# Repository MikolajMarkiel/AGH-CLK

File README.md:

# AGH-CLK
Tiny project of embedded wristwatch based on STM32 realised for University - course Design-Laboratory

## Project assumptions
The main goal was to make self-contained embedded wristwatch module that could be used with dedicated wrist as a complete wristwatch

## Technical specification
-	LCD screen 240x240 1,3 inches
-	Clock precision: -6 sec/day (would be better with capacitor corrections)
-	Current consumption: 54,5 mA (without sleep feature)
-	Estimated lifetime per cycle – around 9h (would be better with implemented sleep feature)
-	Charging: 5 VDC; 400 mA; around 75 minutes to full charge battery 500mAh 

## Overview
This project has been designed for purpose of learning STM32 programming and designing PCB with KiCad software. It won't be supported or improved in future. 
There are many mistakes such as huge current consumption, clock precision or aliased display. It could be of course improved for example by adding sleep feature, but it is not necessary to do right now, because others projects also wait to be designed. 

For more information about the project lets read AGH-CLK-Design_Process_Specification inside "Documentation" folder.

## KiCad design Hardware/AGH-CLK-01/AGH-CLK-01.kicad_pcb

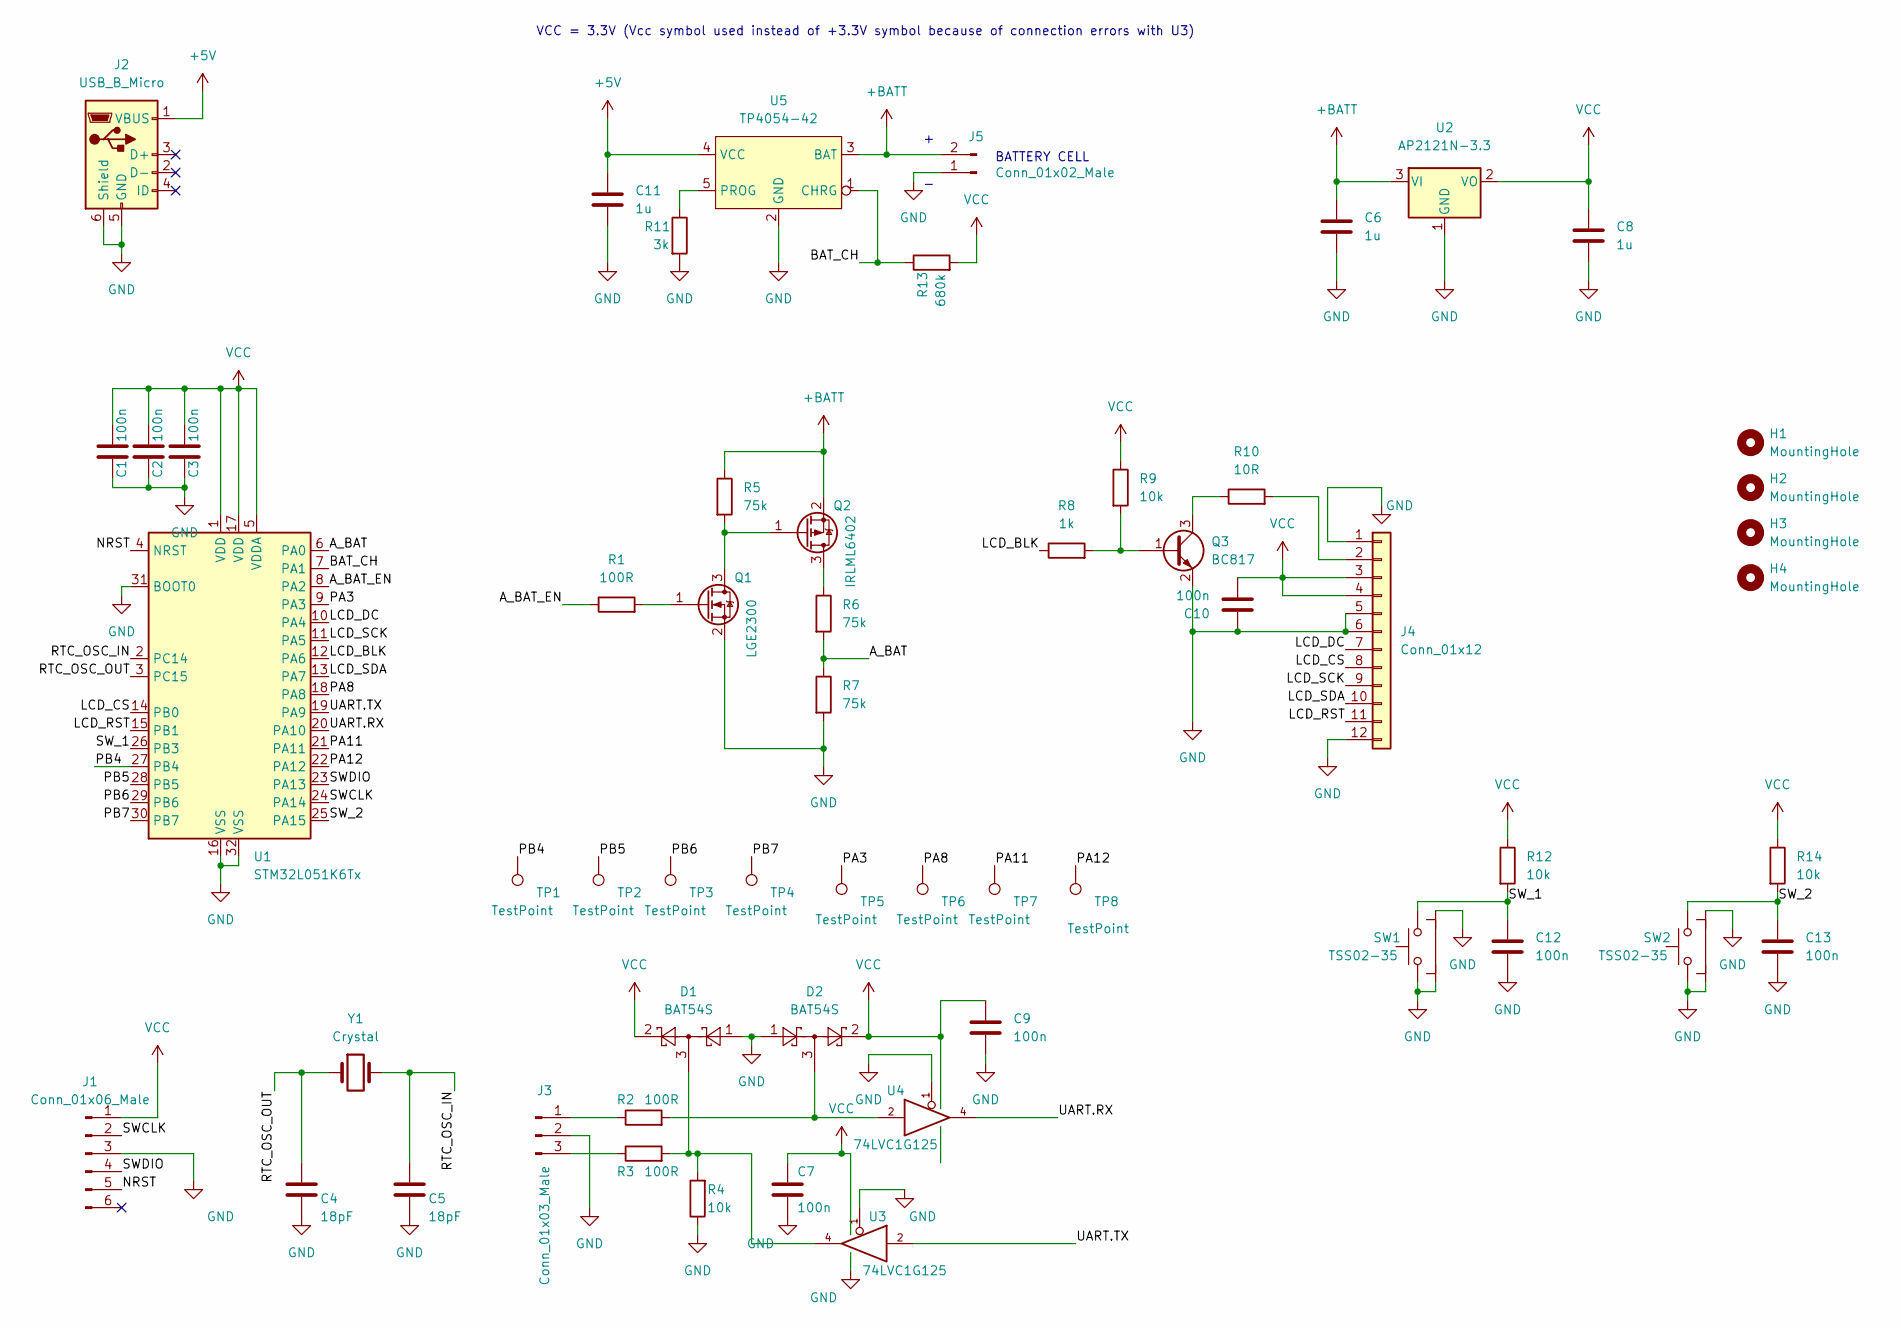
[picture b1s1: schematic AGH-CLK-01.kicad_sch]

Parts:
C1, C2, C3, C7, C9, C10, C12, C13: 100n; C_0805_2012Metric_Pad1.18x1.45mm_HandSolder
C4, C5: 18pF; C_0603_1608Metric_Pad1.08x0.95mm_HandSolder
C6, C8: 1u; C_0805_2012Metric_Pad1.18x1.45mm_HandSolder
C11: 1u; C_1206_3216Metric_Pad1.33x1.80mm_HandSolder
D1, D2: BAT54S; SOT-23
H1, H2, H3, H4: MountingHole; MountingHole_2.2mm_M2_ISO7380
J1: Conn_01x06_Male; PinHeader_2x03_P2.54mm_Vertical
J2: USB_B_Micro; USB_Micro-B_Amphenol_10118194_Horizontal
J3: Conn_01x03_Male; PinHeader_1x03_P2.54mm_Vertical
J4: Conn_01x12; Flex_Tape_12x0.635
J5: Conn_01x02_Male; PinHeader_1x02_P2.54mm_Vertical
Q1: LGE2300; SOT-23
Q2: IRLML6402; SOT-23
Q3: BC817; SOT-23
R1, R2, R3: 100R; R_0603_1608Metric_Pad0.98x0.95mm_HandSolder
R4, R9, R12, R14: 10k; R_0603_1608Metric_Pad0.98x0.95mm_HandSolder
R5, R6, R7: 75k; R_0603_1608Metric_Pad0.98x0.95mm_HandSolder
R8: 1k; R_0603_1608Metric_Pad0.98x0.95mm_HandSolder
R10: 10R; R_0603_1608Metric_Pad0.98x0.95mm_HandSolder
R11: 3k; R_0603_1608Metric_Pad0.98x0.95mm_HandSolder
R13: 680k; R_0805_2012Metric_Pad1.20x1.40mm_HandSolder
SW1, SW2: TSS02-35; SW_SPST_TSS02-035NT
TP1, TP2, TP3, TP4, TP5, TP6, TP7, TP8: TestPoint; TestPoint_Pad_1.5x1.5mm
U1: STM32L051K6Tx; LQFP-32_7x7mm_P0.8mm
U2: AP2121N-3.3; SOT-23
U3, U4: 74LVC1G125; SOT-23-5_HandSoldering
U5: TP4054-42; SOT-23-5_HandSoldering
Y1: Crystal; Crystal_SMD_3215-2Pin_3.2x1.5mm

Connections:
+5V: C11.1, J2.1 (VBUS), U5.4 (VCC)
+BATT: C6.1, J5.2, Q2.2 (S), R5.1, U2.3 (VI), U5.3 (BAT)
/A_BAT: R6.2, R7.1, U1.6 (PA0)
/A_BAT_EN: R1.1, U1.8 (PA2)
/BAT_CH: R13.1, U1.7 (PA1), U5.1 (CHRG)
/LCD_BLK: R8.1, U1.12 (PA6)
/LCD_CS: J4.8, U1.14 (PB0)
/LCD_DC: J4.7, U1.10 (PA4)
/LCD_RST: J4.11, U1.15 (PB1)
/LCD_SCK: J4.9, U1.11 (PA5)
/LCD_SDA: J4.10, U1.13 (PA7)
/NRST: J1.5, U1.4 (NRST)
/PA3: TP5.1, U1.9 (PA3)
/PA8: TP6.1, U1.18 (PA8)
/PA11: TP7.1, U1.21 (PA11)
/PA12: TP8.1, U1.22 (PA12)
/PB4: TP1.1, U1.27 (PB4)
/PB5: TP2.1, U1.28 (PB5)
/PB6: TP3.1, U1.29 (PB6)
/PB7: TP4.1, U1.30 (PB7)
/RTC_OSC_IN: C5.1, U1.2 (PC14), Y1.2
/RTC_OSC_OUT: C4.1, U1.3 (PC15), Y1.1
/SWCLK: J1.2, U1.24 (PA14)
/SWDIO: J1.4, U1.23 (PA13)
/SW_1: C12.1, R12.2, SW1.2, U1.26 (PB3)
/SW_2: C13.1, R14.2, SW2.2, U1.25 (PA15)
/UART.RX: U1.20 (PA10), U4.4
/UART.TX: U1.19 (PA9), U3.2
GND: C1.2, C2.2, C3.2, C4.2, C5.2, C6.2, C7.2, C8.2, C9.2, C10.1, C11.2, C12.2, C13.2, D1.1, D2.1, J1.3, J2.5 (GND), J2.6 (Shield), J3.2, J4.1, J4.5, J4.6, J4.12, J5.1, Q1.2 (S), Q3.2 (E), R4.1, R7.2, R11.2, SW1.1, SW1.3, SW1.4, SW2.1, SW2.3, SW2.4, U1.16 (VSS), U1.31 (BOOT0), U1.32 (VSS), U2.1 (GND), U3.1, U3.3 (GND), U4.1, U4.3 (GND), U5.2 (GND)
unnamed: D1.3, R3.2, R4.2, U3.4
unnamed: D2.3, R2.2, U4.2
unnamed: J3.1, R2.1
unnamed: J3.3, R3.1
unnamed: J4.2, R10.2
unnamed: Q1.1 (G), R1.2
unnamed: Q1.3 (D), Q2.1 (G), R5.2
unnamed: Q2.3 (D), R6.1
unnamed: Q3.1 (B), R8.2, R9.2
unnamed: Q3.3 (C), R10.1
unnamed: R11.1, U5.5 (PROG)
VCC: C1.1, C2.1, C3.1, C7.1, C8.1, C9.1, C10.2, D1.2, D2.2, J1.1, J4.3, J4.4, R9.1, R12.1, R13.2, R14.1, U1.1 (VDD), U1.5 (VDDA), U1.17 (VDD), U2.2 (VO), U3.5 (VCC), U4.5 (VCC)

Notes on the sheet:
VCC = 3.3V (Vcc symbol used instead of +3.3V symbol because of connection errors with U3)
BATTERY CELL

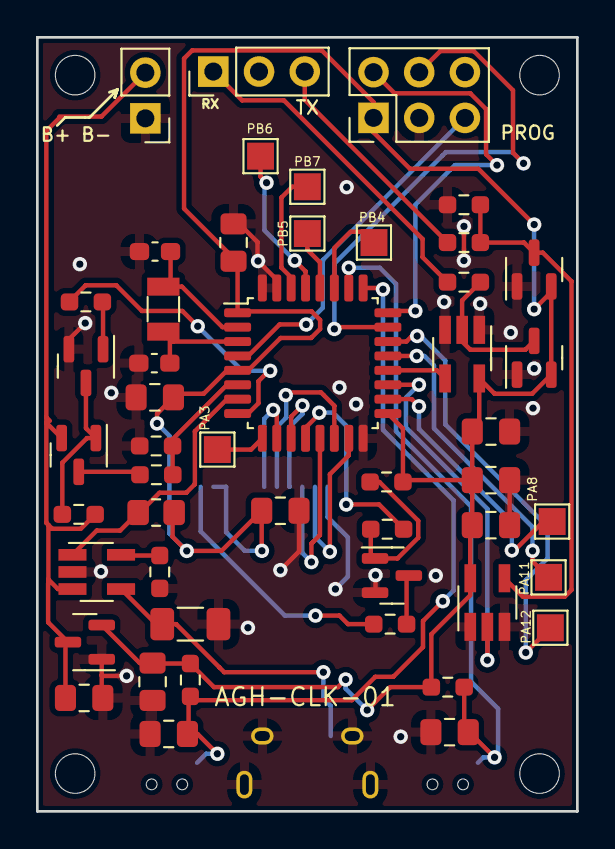
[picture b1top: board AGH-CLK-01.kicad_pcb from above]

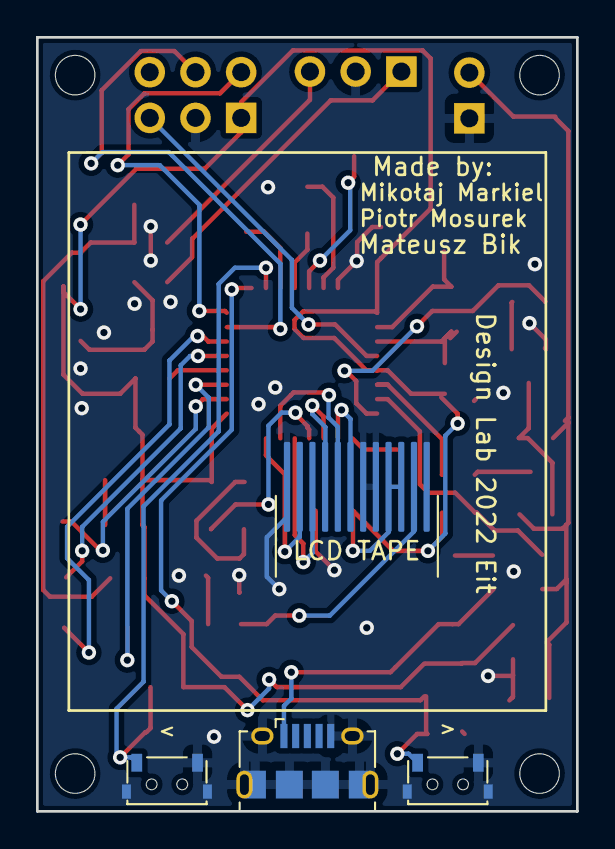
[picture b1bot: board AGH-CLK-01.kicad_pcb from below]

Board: 2 copper layers, 30.0 x 43.0 mm, 57 parts (4 on the bottom side), 41 nets.

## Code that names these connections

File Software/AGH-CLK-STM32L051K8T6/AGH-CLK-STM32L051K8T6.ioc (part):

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Mcu.Name=STM32L051K(6-8)Tx
Mcu.Package=LQFP32
Mcu.UserName=STM32L051K8Tx
PA0.GPIOParameters=GPIO_Label
PA0.GPIO_Label=A_BAT
PA0.Mode=IN0
PA0.Signal=ADC_IN0
PA1.GPIOParameters=GPIO_Label
PA1.GPIO_Label=BAT_CH
PA1.Signal=GPIO_Input
PA10.Mode=Asynchronous
PA10.Signal=USART1_RX
PA13.Mode=Serial_Wire
PA13.Signal=SYS_SWDIO
PA14.Mode=Serial_Wire
PA14.Signal=SYS_SWCLK
PA15.GPIOParameters=GPIO_Label
PA15.GPIO_Label=SW2
PA15.Signal=GPIO_Input
PA2.GPIOParameters=PinState,GPIO_Label
PA2.GPIO_Label=A_BAT_EN
PA2.PinState=GPIO_PIN_SET
PA2.Signal=GPIO_Output
PA4.GPIOParameters=GPIO_Speed,GPIO_Label
PA4.GPIO_Label=LCD_DC
PA4.GPIO_Speed=GPIO_SPEED_FREQ_VERY_HIGH
PA4.Signal=GPIO_Output
PA5.GPIOParameters=GPIO_Label
PA5.GPIO_Label=LCD_SCK
PA5.Mode=Simplex_Bidirectional_Master
PA5.Signal=SPI1_SCK
PA6.GPIOParameters=PinState,GPIO_Label
PA6.GPIO_Label=LCD_BLK
PA6.PinState=GPIO_PIN_SET
PA6.Signal=GPIO_Output
PA7.GPIOParameters=GPIO_Label
PA7.GPIO_Label=LCD_SDA
PA7.Mode=Simplex_Bidirectional_Master
PA7.Signal=SPI1_MOSI
PA9.Mode=Asynchronous
PA9.Signal=USART1_TX
PB0.GPIOParameters=GPIO_Speed,GPIO_Label
PB0.GPIO_Label=LCD_CS
PB0.GPIO_Speed=GPIO_SPEED_FREQ_VERY_HIGH
PB0.Signal=GPIO_Output
PB1.GPIOParameters=GPIO_Label
PB1.GPIO_Label=LCD_RST
PB1.Signal=GPIO_Output
PB3.GPIOParameters=GPIO_Label
PB3.GPIO_Label=SW1
PB3.Signal=GPIO_Input
PC14-OSC32_IN.Mode=LSE-External-Oscillator
PC14-OSC32_IN.Signal=RCC_OSC32_IN
PC15-OSC32_OUT.Mode=LSE-External-Oscillator
PC15-OSC32_OUT.Signal=RCC_OSC32_OUT
RCC.SYSCLKFreq_VALUE=32000000
RCC.SYSCLKSource=RCC_SYSCLKSOURCE_PLLCLK
board=custom

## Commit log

2023-01-20 v1.0_20.01.2023_AGH-CLK
    Added full documentation of this project
